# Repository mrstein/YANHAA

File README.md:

# YANHAA
YANHAA - You Are Not Heartless After All is an electronical stethoscope based on a MK20DX256 (TEENSY 3.2).
Still Work In Progress, the 3D files are not finished yet.

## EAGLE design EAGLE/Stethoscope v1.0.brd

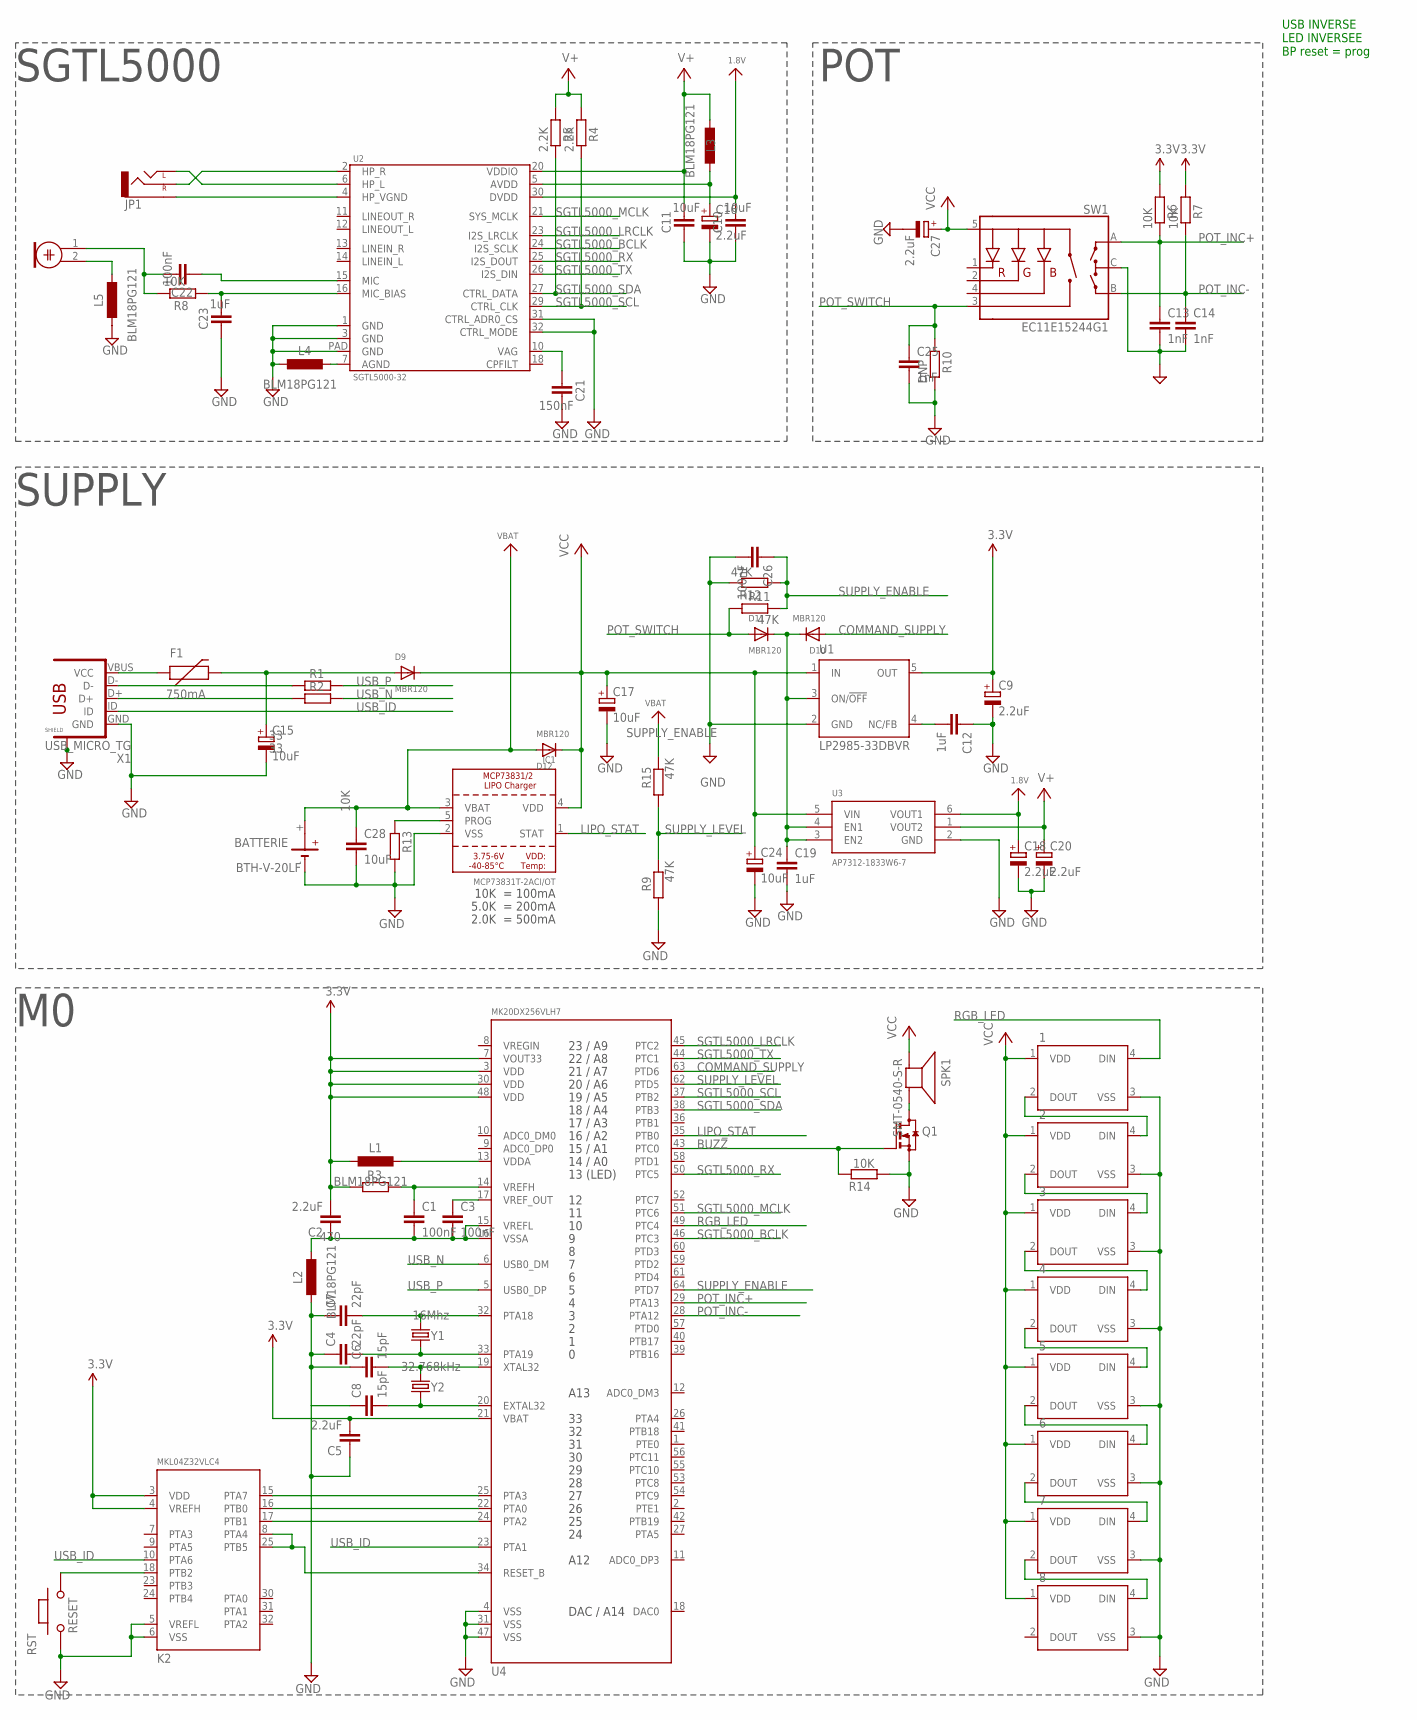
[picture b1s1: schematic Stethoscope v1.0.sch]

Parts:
1, 2, 3, 4, 5, 6, 7, 8: WS2812B
BATTERIE: BTH-V-20LF; 3V_BAT_HOLDER
C1, C3, C26: 100nF; C0603
C2, C5: 2.2uF; C0603
C4, C7: 22pF; C0603
C6, C8: 15pF; C0603
C9, C16, C18, C20, C27: 2.2uF; C0805POL
C10, C11: 10uF; C0805
C12, C19: 1uF; C0603
C13, C14, C25: 1nF; C0603
C15, C17, C24: 10uF; C0805POL
C21: 150nF; C0805
C22: 100nF; C0805
C23: 1uF; C0805
C28: 10uF; C1206
D9, D10, D11, D12: MBR120; SOD-323F
F1: 750mA; 0603
IC1: MCP73831T-2ACI/OT; SOT23-5
JP1: AUDIO-JACK1:1; STEREOJACK2.5MM
K2: MKL04Z32VLC4; LQFP32-08
L1, L2, L3, L4, L5: BLM18PG121; L0603
M1: ELECTRET_MICROPHON-F6050AP; F6050AP
Q1: BSS123; SOT23
R1, R2: 33; R0603
R3: 470; R0603
R4, R5: 2.2K; R0603
R6, R7, R8, R13, R14: 10K; R0603
R9, R11, R12, R15: 47K; R0603
R10: DNP; R0603
RST: RESET; 157SW
SPK1: SMT-0540-S-R
SW1: EC11E15244G1; ENCODER_LED_3_KIT
U1: LP2985-33DBVR; SOT23-DBV
U2: SGTL5000-32; QFN-32-5MM
U3: AP7312-1833W6-7; SOT23-6
U4: MK20DX256VLH7; LQFP64-05
X1: USB_MICRO_TG
Y1: 16Mhz; CRYSTAL-SMD-3.2X1.5MM
Y2: 32.768kHz; CRYSTAL-SMD-3.2X1.5MM

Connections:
1.8V: C10.2, C18.SMD+ (+), U2.30 (DVDD), U3.6 (VOUT1)
3.3V: C2.2, C5.2, C9.SMD+ (+), K2.3 (VDD), K2.4 (VREFH), L1.2, R3.2, R6.2, R7.2, U1.5 (OUT), U4.3 (VDD), U4.7 (VOUT33), U4.21 (VBAT), U4.30 (VDD), U4.48 (VDD)
BUZZ: Q1.1 (G), R14.2, U4.43 (PTC0)
COMMAND_SUPPLY: D10.A, U4.63 (PTD6)
COMMAND_SUPPLY2: C19.1, D10.C, D11.C, U1.3 (ON/!OFF), U3.3 (EN2), U3.4 (EN1)
GND: 1.3 (VSS), 2.3 (VSS), 3.3 (VSS), 4.3 (VSS), 5.3 (VSS), 6.3 (VSS), 7.3 (VSS), 8.3 (VSS), BATTERIE.-, C4.1, C5.1, C6.1, C7.1, C8.1, C9.SMD- (-), C10.1, C11.1, C12.1, C13.2, C14.2, C15.SMD- (-), C16.SMD- (-), C17.SMD- (-), C18.SMD- (-), C19.2, C20.SMD- (-), C21.2, C23.1, C24.SMD- (-), C25.2, C26.2, C27.SMD- (-), C28.2, IC1.2 (VSS), K2.5 (VREFL), K2.6 (VSS), L2.2, L4.2, L5.2, Q1.2 (S), R9.1, R10.1, R12.2, R13.1, R14.1, RST.1, SW1.C, U1.2 (GND), U2.1 (GND), U2.3 (GND), U2.31 (CTRL_ADR0_CS), U2.32 (CTRL_MODE), U2.PAD (GND), U3.2 (GND), U4.4 (VSS), U4.31 (VSS), U4.47 (VSS), X1.GND, X1.SHIELD, X1.SHIELD2 (SHIELD1), X1.SHIELD3 (SHIELD2), X1.SHIELD4 (SHIELD3), X1.SHIELD5 (SHIELD4), X1.SHIELD6 (SHIELD5), X1.SHIELD7 (SHIELD6), X1.SHIELD8 (SHIELD7)
LIPO_STAT: IC1.1 (STAT), U4.35 (PTB0)
unnamed: C16.SMD+ (+), L3.1, U2.5 (AVDD)
unnamed: L1.1, U4.13 (VDDA)
unnamed: K2.8 (PTA4), K2.25 (PTB5), U4.34 (RESET_B)
unnamed: C21.1, U2.10 (VAG)
unnamed: C6.2, U4.19 (XTAL32), Y2.P$2 (2)
unnamed: C15.SMD+ (+), D9.A, F1.2
unnamed: C23.2, R8.2, U2.16 (MIC_BIAS)
unnamed: C22.1, U2.15 (MIC)
unnamed: JP1.5 (SLEEVE), U2.4 (HP_VGND)
unnamed: JP1.1 (LEFT), U2.6 (HP_L)
unnamed: JP1.4 (RIGHT), U2.2 (HP_R)
unnamed: C8.2, U4.20 (EXTAL32), Y2.P$1 (1)
unnamed: C22.2, M1.1, R8.1
unnamed: R1.2, X1.D-
unnamed: R2.2, X1.D+
unnamed: L5.1, M1.2
unnamed: IC1.5 (PROG), R13.2
unnamed: L4.1, U2.7 (AGND)
unnamed: C12.2, U1.4 (NC/FB)
unnamed: C7.2, U4.32 (PTA18), Y1.P$2 (2)
unnamed: C4.2, U4.33 (PTA19), Y1.P$1 (1)
unnamed: F1.1, X1.VBUS (VCC)
unnamed: C1.1, R3.1, U4.14 (VREFH)
unnamed: C1.2, C2.1, C3.2, L2.1, U4.15 (VREFL), U4.16 (VSSA)
unnamed: C3.1, U4.17 (VREF_OUT)
unnamed: K2.15 (PTA7), U4.25 (PTA3)
unnamed: K2.16 (PTB0), U4.22 (PTA0)
unnamed: K2.17 (PTB1), U4.24 (PTA2)
unnamed: K2.18 (PTB2), RST.2
unnamed: 2.2 (DOUT), 3.4 (DIN)
unnamed: 3.2 (DOUT), 4.4 (DIN)
unnamed: 4.2 (DOUT), 5.4 (DIN)
unnamed: 5.2 (DOUT), 6.4 (DIN)
unnamed: 6.2 (DOUT), 7.4 (DIN)
unnamed: Q1.3 (D), SPK1.+ (-)
unnamed: 7.2 (DOUT), 8.4 (DIN)
unnamed: 1.2 (DOUT), 2.4 (DIN)
POT_INC+: C13.1, R6.1, SW1.A, U4.29 (PTA13)
POT_INC-: C14.1, R7.1, SW1.B, U4.28 (PTA12)
POT_SWITCH: C25.1, D11.A, R10.2, R11.1, SW1.3 (SW)
RGB_LED: 1.4 (DIN), U4.49 (PTC4)
SGTL5000_BCLK: U2.24 (I2S_SCLK), U4.46 (PTC3)
SGTL5000_LRCLK: U2.23 (I2S_LRCLK), U4.45 (PTC2)
SGTL5000_MCLK: U2.21 (SYS_MCLK), U4.51 (PTC6)
SGTL5000_RX: U2.25 (I2S_DOUT), U4.50 (PTC5)
SGTL5000_SCL: R4.1, U2.29 (CTRL_CLK), U4.37 (PTB2)
SGTL5000_SDA: R5.1, U2.27 (CTRL_DATA), U4.38 (PTB3)
SGTL5000_TX: U2.26 (I2S_DIN), U4.44 (PTC1)
SUPPLY_ENABLE: C26.1, R11.2, R12.1, U4.64 (PTD7)
SUPPLY_LEVEL: R9.2, R15.1, U4.62 (PTD5)
USB_ID: K2.10 (PTA6), U4.23 (PTA1), X1.ID
USB_N: R2.1, U4.6 (USB0_DM)
USB_P: R1.1, U4.5 (USB0_DP)
V+: C11.2, C20.SMD+ (+), L3.2, R4.2, R5.2, U2.20 (VDDIO), U3.1 (VOUT2)
VBAT: BATTERIE.+, C28.1, D12.A, IC1.3 (VBAT), R15.2
VCC: 1.1 (VDD), 2.1 (VDD), 3.1 (VDD), 4.1 (VDD), 5.1 (VDD), 6.1 (VDD), 7.1 (VDD), 8.1 (VDD), C17.SMD+ (+), C24.SMD+ (+), C27.SMD+ (+), D9.C, D12.C, IC1.4 (VDD), SPK1.- (+), SW1.5 (+), U1.1 (IN), U3.5 (VIN)

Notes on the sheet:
10K = 100mA
5.0K = 200mA
2.0K = 500mA
SGTL5000
SUPPLY
POT
23 / A9
22 / A8
21 / A7
20 / A6
19 / A5
18 / A4
17 / A3
16 / A2
15 / A1
14 / A0
13 (LED)
A13
A12
DAC / A14
USB INVERSE LED INVERSEE BP reset = prog

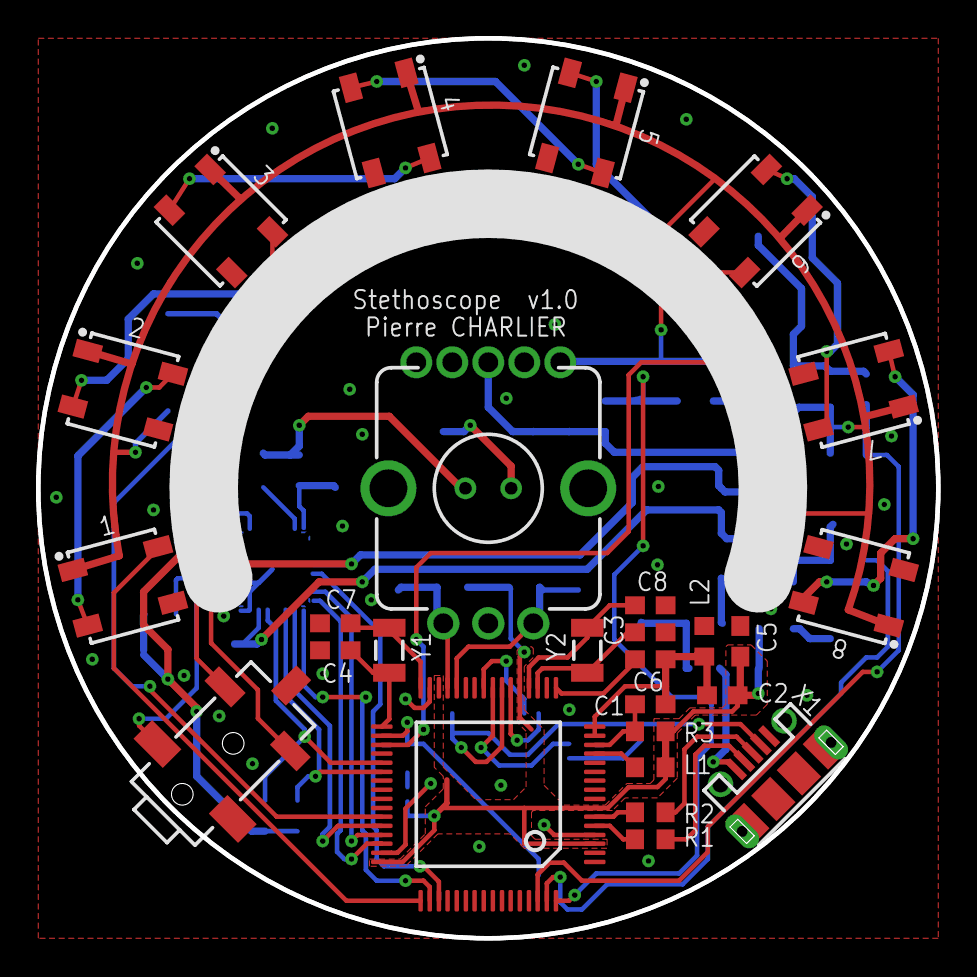
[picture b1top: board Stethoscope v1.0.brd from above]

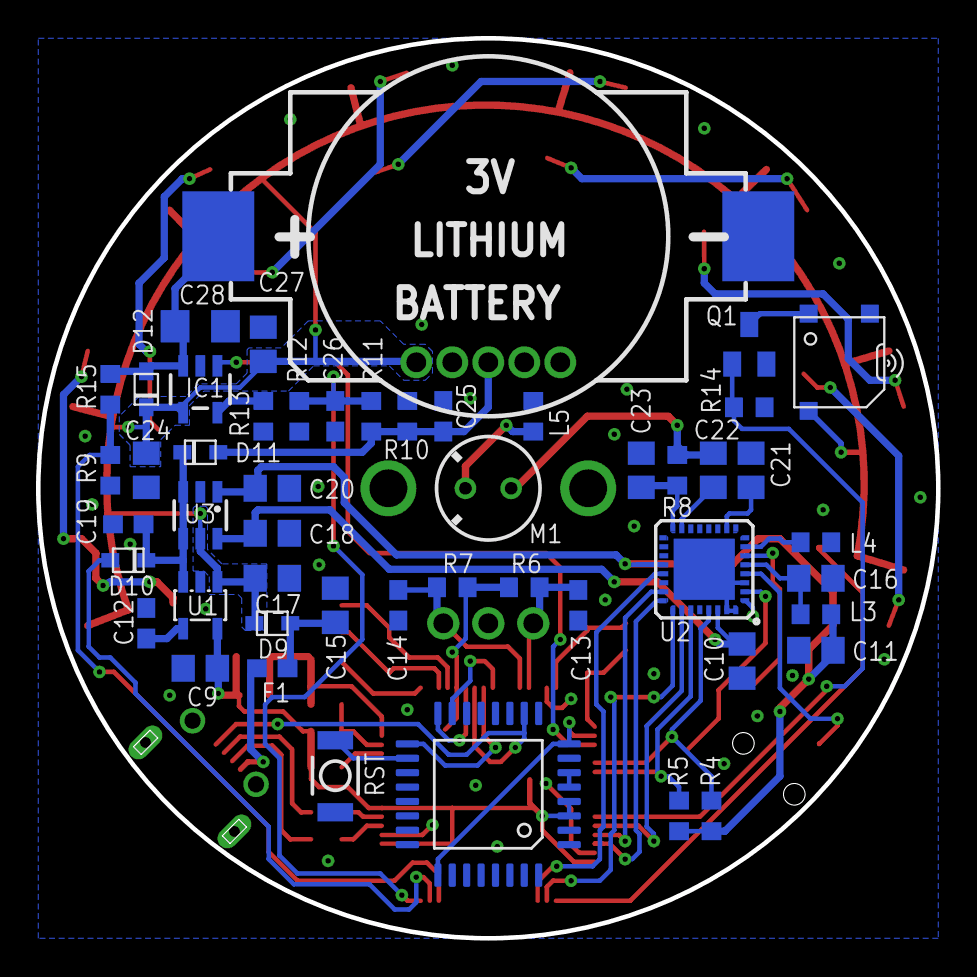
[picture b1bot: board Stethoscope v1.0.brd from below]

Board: 2 copper layers, 50.0 x 50.0 mm, 77 parts (50 on the bottom side), 63 nets.

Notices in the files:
parts and their libraries:
SparkFun-PowerIC: Licensing: Creative Commons ShareAlike 4.0 International - https://creativecommons.org/licenses/by-sa/4.0
